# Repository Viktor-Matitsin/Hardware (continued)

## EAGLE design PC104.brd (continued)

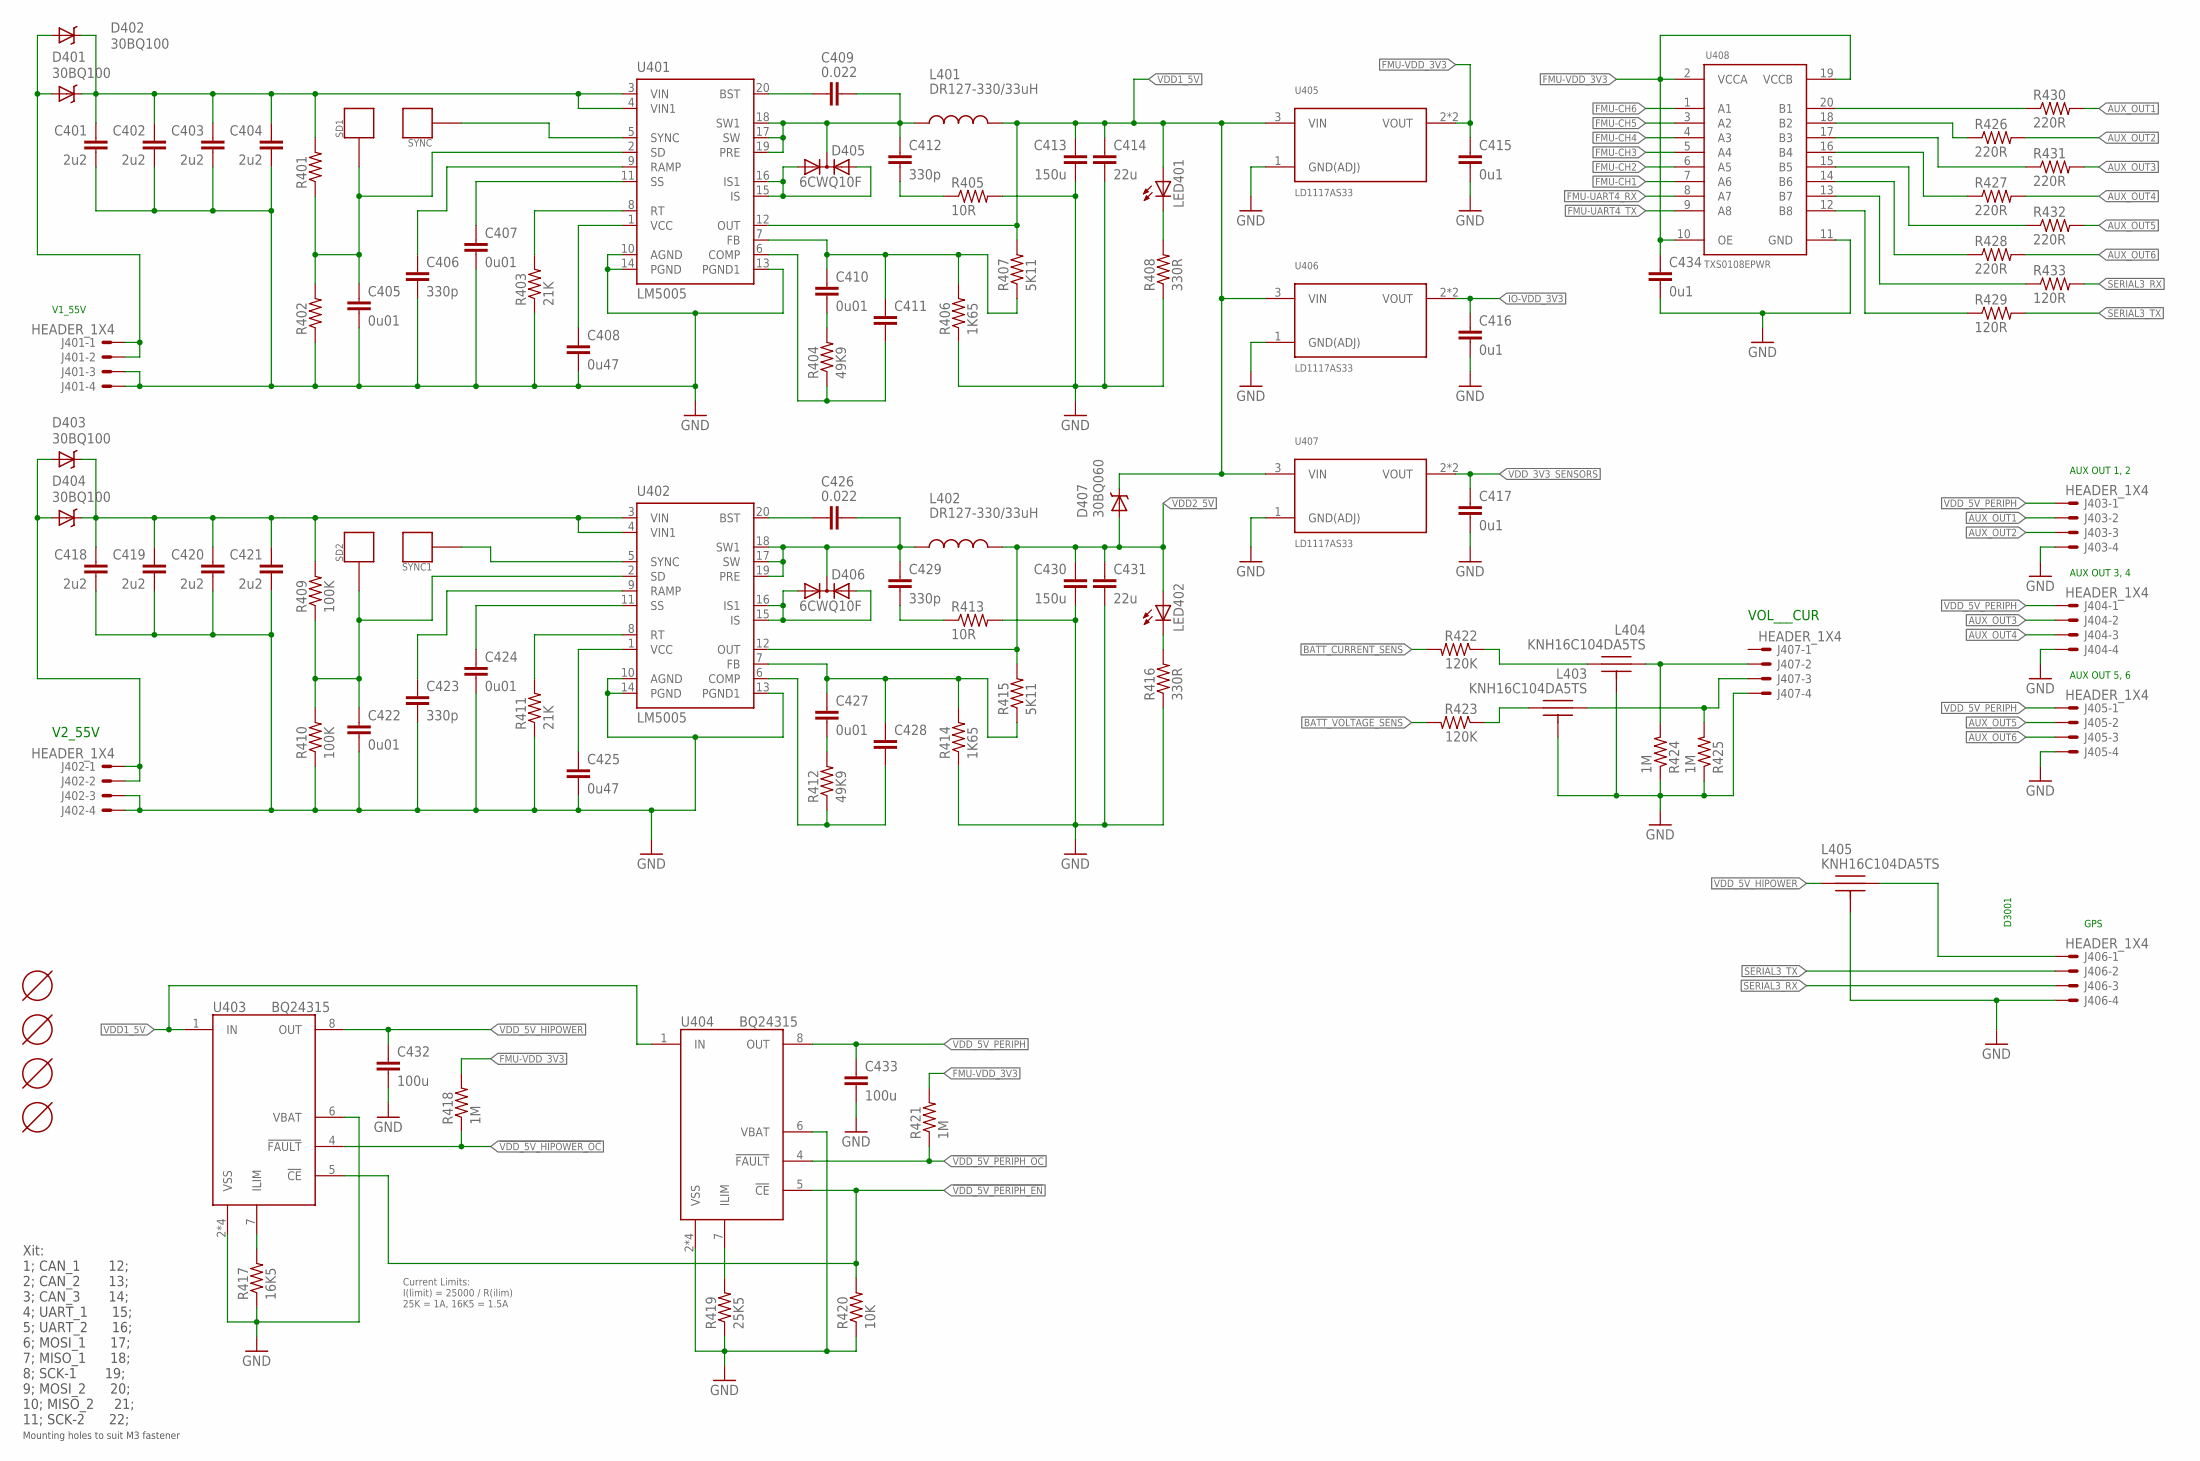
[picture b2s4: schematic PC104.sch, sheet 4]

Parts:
C401, C402, C403, C404, C418, C419, C420, C421: 2u2; 1812-CAP
C405, C407, C410, C422, C424, C427: 0u01; 0805-CAP
C406, C412, C423, C429: 330p; 0805-CAP
C408, C425: 0u47; 0805-CAP
C409, C426: 0.022; 0805-CAP
C411, C428: CAP0805; 0805-CAP
C413, C430: 150u; 1206-CAP
C414, C431: 22u; 1206-CAP
C415, C416, C417: 0u1; 0805-CAP
C432, C433: 100u; 1206-CAP
C434: 0u1; 0603-CAP
D401, D402, D403, D404: 30BQ100; SMA-DIODE
D405, D406: 6CWQ10F; SOT23
D407: 30BQ060; SMA-DIODE
J401, J402, J403, J404, J405, J406, J407: HEADER_1X4; HEADER_2.54MM-1X04
L401, L402: DR127-330/33uH; SLF10145
L403, L404, L405: KNH16C104DA5TS; KYOCERA-KNH16-DA
LED401, LED402: LED0603; 0603-LED
R401, R402: RESISTOR0805; 0805
R403, R411: 21K; 0805
R404, R412: 49K9; 0805
R405, R413: 10R; R2512
R406, R414: 1K65; 0805
R407, R415: 5K11; 0805
R408, R416: 330R; 0805
R409, R410: 100K; 0805
R417: 16K5; 0603-RES
R418, R421, R424, R425: 1M; 0603-RES
R419: 25K5; 0603-RES
R420: 10K; 0603-RES
R422, R423: 120K; 0603-RES
R426, R427, R428, R430, R431, R432: 220R; 0603-RES
R429, R433: 120R; 0603-RES
SD1, SD2: CYNC; PAD.03X.03
SYNC, SYNC1: CYNC; PAD.03X.03
U401, U402: LM5005; TSSOP20
U403, U404: BQ24315; QFN8-DSG
U405, U406, U407: LD1117AS33; SOT-223
U408: TXS0108EPWR; R-PDSO-G20
U$1, U$2, U$3, U$4: MOUNT-HOLE; MOUNT-HOLE3.3

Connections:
!VDD_5V_HIPOWER_OC: R418.1, U403.4 (!FAULT); also elsewhere on the board
!VDD_5V_PERIPH_EN: R420.2, U403.5 (!CE), U404.5 (!CE); also elsewhere on the board
!VDD_5V_PERIPH_OC: R421.1, U404.4 (!FAULT); also elsewhere on the board
+55V1: D401.A, D402.A, J401.1, J401.2
+55V1_V: C401.1, C402.1, C403.1, C404.1, D401.C, D402.C, R401.2, U401.3 (VIN), U401.4 (VIN1)
+55V2: D403.A, D404.A, J402.1, J402.2
+55V2_V: C418.1, C419.1, C420.1, C421.1, D403.C, D404.C, R409.2, U402.3 (VIN), U402.4 (VIN1)
AUX_OUT1: J403.2, R430.2
AUX_OUT2: J403.3, R426.2
AUX_OUT3: J404.2, R431.2
AUX_OUT4: J404.3, R427.2
AUX_OUT5: J405.2, R432.2
AUX_OUT6: J405.3, R428.2
BATT_CURRENT_SENS: R422.2; also elsewhere on the board
BATT_VOLTAGE_SENS: R423.2; also elsewhere on the board
D1X: C409.P$1 (1), C412.P$1 (1), D405.3 (C), L401.P$1 (1), U401.17 (SW), U401.18 (SW1), U401.19 (PRE)
D1_O: D405.1 (A1), D405.2 (A2), U401.15 (IS), U401.16 (IS1)
D2X: C426.P$1 (1), C429.P$1 (1), D406.3 (C), L402.P$1 (1), U402.17 (SW), U402.18 (SW1), U402.19 (PRE)
D2_O: D406.1 (A1), D406.2 (A2), U402.15 (IS), U402.16 (IS1)
FMU-CH1: U408.7 (A6); also elsewhere on the board
FMU-CH2: U408.6 (A5); also elsewhere on the board
FMU-CH3: U408.5 (A4); also elsewhere on the board
FMU-CH4: U408.4 (A3); also elsewhere on the board
FMU-CH5: U408.3 (A2); also elsewhere on the board
FMU-CH6: U408.1 (A1); also elsewhere on the board
FMU-UART4_RX: U408.8 (A7); also elsewhere on the board
FMU-UART4_TX: U408.9 (A8); also elsewhere on the board
FMU-VDD_3V3: C415.P$1 (1), C434.P$1 (1), R418.2, R421.2, U405.2 (VOUT), U405.4 (VOUT), U408.2 (VCCA), U408.10 (OE), U408.19 (VCCB); also elsewhere on the board
GND: C401.2, C402.2, C403.2, C404.2, C405.P$2 (2), C406.P$2 (2), C407.P$2 (2), C408.P$2 (2), C413.P$2 (2), C414.P$2 (2), C415.P$2 (2), C416.P$2 (2), C417.P$2 (2), C418.2, C419.2, C420.2, C421.2, C422.P$2 (2), C423.P$2 (2), C424.P$2 (2), C425.P$2 (2), C430.P$2 (2), C431.P$2 (2), C432.P$2 (2), C433.P$2 (2), C434.P$2 (2), J401.3, J401.4, J402.3, J402.4, J403.4, J404.4, J405.4, J406.4, J407.4, L403.P$3, L403.P$4, L403.P$5, L404.P$3, L404.P$4, L404.P$5, L405.P$3, L405.P$4, L405.P$5, R402.1, R403.1, R405.2, R406.1, R408.1, R410.1, R411.1, R413.2, R414.1, R416.1, R417.1, R419.1, R420.1, R424.1, R425.1, U401.10 (AGND), U401.13 (PGND1), U401.14 (PGND), U402.10 (AGND), U402.13 (PGND1), U402.14 (PGND), U403.2 (VSS), U403.6 (VBAT), U403.GND (VSS), U403.P$2 (VSS), U403.P$3 (VSS), U404.2 (VSS), U404.6 (VBAT), U404.GND (VSS), U404.P$2 (VSS), U404.P$3 (VSS), U405.1 (GND(ADJ)), U406.1 (GND(ADJ)), U407.1 (GND(ADJ)), U408.11 (GND); also elsewhere on the board
GPS: J406.1, L405.P$2
IO-VDD_3V3: C416.P$1 (1), U406.2 (VOUT), U406.4 (VOUT); also elsewhere on the board
unnamed: SYNC.P$1, U401.5 (SYNC)
unnamed: SYNC1.P$1, U402.5 (SYNC)
unnamed: L404.P$2, R422.1
unnamed: L403.P$2, R423.1
unnamed: J407.2, L404.P$1, R424.2
unnamed: J407.3, L403.P$1, R425.2
unnamed: R433.1, U408.13 (B7)
unnamed: C405.P$1 (1), R401.1, R402.2, SD1.P$1, U401.2 (SD)
unnamed: C412.P$2 (2), R405.1
unnamed: R429.1, U408.12 (B8)
unnamed: LED402.C, R416.2
unnamed: C407.P$1 (1), U401.11 (SS)
unnamed: C411.P$2 (2), R404.1, U401.6 (COMP)
unnamed: R403.2, U401.8 (RT)
unnamed: C409.P$2 (2), U401.20 (BST)
unnamed: C408.P$1 (1), U401.1 (VCC)
unnamed: LED401.C, R408.2
unnamed: R417.2, U403.7 (ILIM)
unnamed: C423.P$1 (1), U402.9 (RAMP)
unnamed: C410.P$1 (1), C411.P$1 (1), R406.2, R407.1, U401.7 (FB)
unnamed: C410.P$2 (2), R404.2
unnamed: C422.P$1 (1), R409.1, R410.2, SD2.P$1, U402.2 (SD)
unnamed: C424.P$1 (1), U402.11 (SS)
unnamed: R411.2, U402.8 (RT)
unnamed: C425.P$1 (1), U402.1 (VCC)
unnamed: C406.P$1 (1), U401.9 (RAMP)
unnamed: R430.1, U408.20 (B1)
unnamed: R426.1, U408.18 (B2)
unnamed: R431.1, U408.17 (B3)
unnamed: R427.1, U408.16 (B4)
unnamed: R432.1, U408.15 (B5)
unnamed: R428.1, U408.14 (B6)
unnamed: C426.P$2 (2), U402.20 (BST)
unnamed: C428.P$2 (2), R412.1, U402.6 (COMP)
unnamed: C429.P$2 (2), R413.1
unnamed: R419.2, U404.7 (ILIM)
unnamed: C427.P$1 (1), C428.P$1 (1), R414.2, R415.1, U402.7 (FB)
unnamed: C427.P$2 (2), R412.2
SERIAL3_RX: J406.3, R433.2
SERIAL3_TX: J406.2, R429.2
VDD1_5V: C413.P$1 (1), C414.P$1 (1), D407.C, L401.P$2 (2), LED401.A, R407.2, U401.12 (OUT), U403.1 (IN), U404.1 (IN), U405.3 (VIN), U406.3 (VIN), U407.3 (VIN); also elsewhere on the board
VDD2_5V: C430.P$1 (1), C431.P$1 (1), D407.A, L402.P$2 (2), LED402.A, R415.2, U402.12 (OUT)
VDD_3V3_SENSORS: C417.P$1 (1), U407.2 (VOUT), U407.4 (VOUT); also elsewhere on the board
VDD_5V_HIPOWER: C432.P$1 (1), L405.P$1, U403.8 (OUT); also elsewhere on the board
VDD_5V_PERIPH: C433.P$1 (1), J403.1, J404.1, J405.1, U404.8 (OUT); also elsewhere on the board

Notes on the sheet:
Mounting holes to suit M3 fastener
Xit: 1; CAN_1 12; 2; CAN_2 13; 3; CAN_3 14; 4; UART_1 15; 5; UART_2 16; 6; MOSI_1 17; 7; MISO_1 18; 8; SCK-1 19; 9; MOSI_2 20; 10; MISO_2 21; 11; SCK-2 22;
AUX OUT 1, 2
AUX OUT 3, 4
AUX OUT 5, 6
V1_55V
Current Limits: I(limit) = 25000 / R(ilim) 25K = 1A, 16K5 = 1.5A
D3001
GPS
VOL___CUR
V2_55V

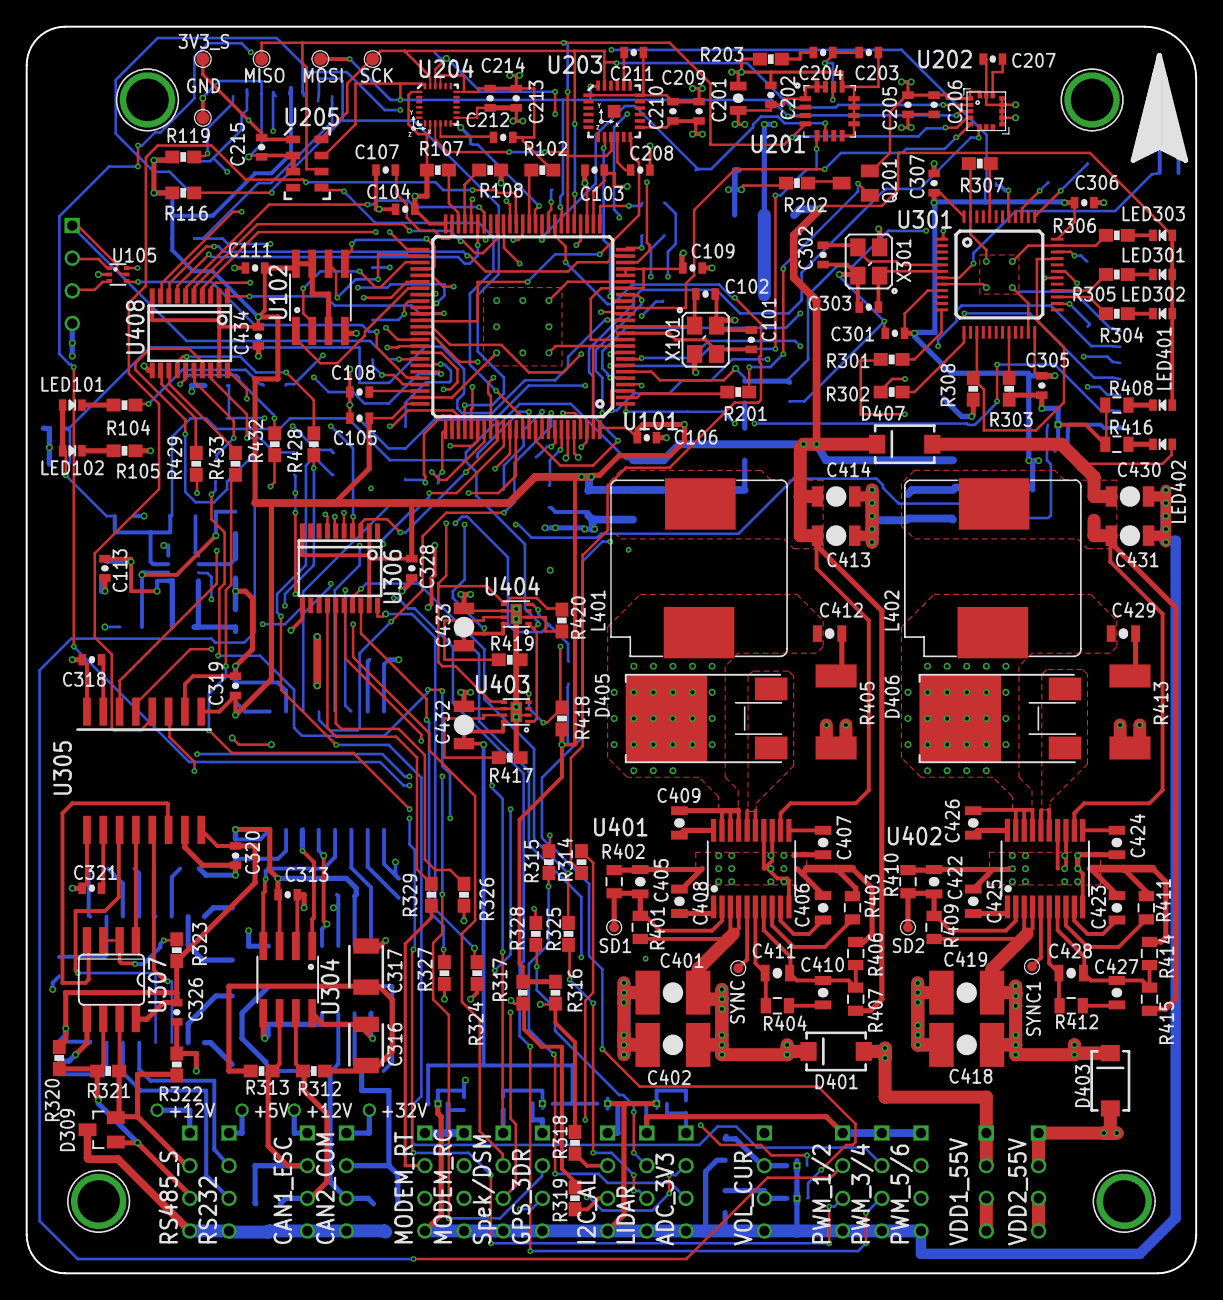
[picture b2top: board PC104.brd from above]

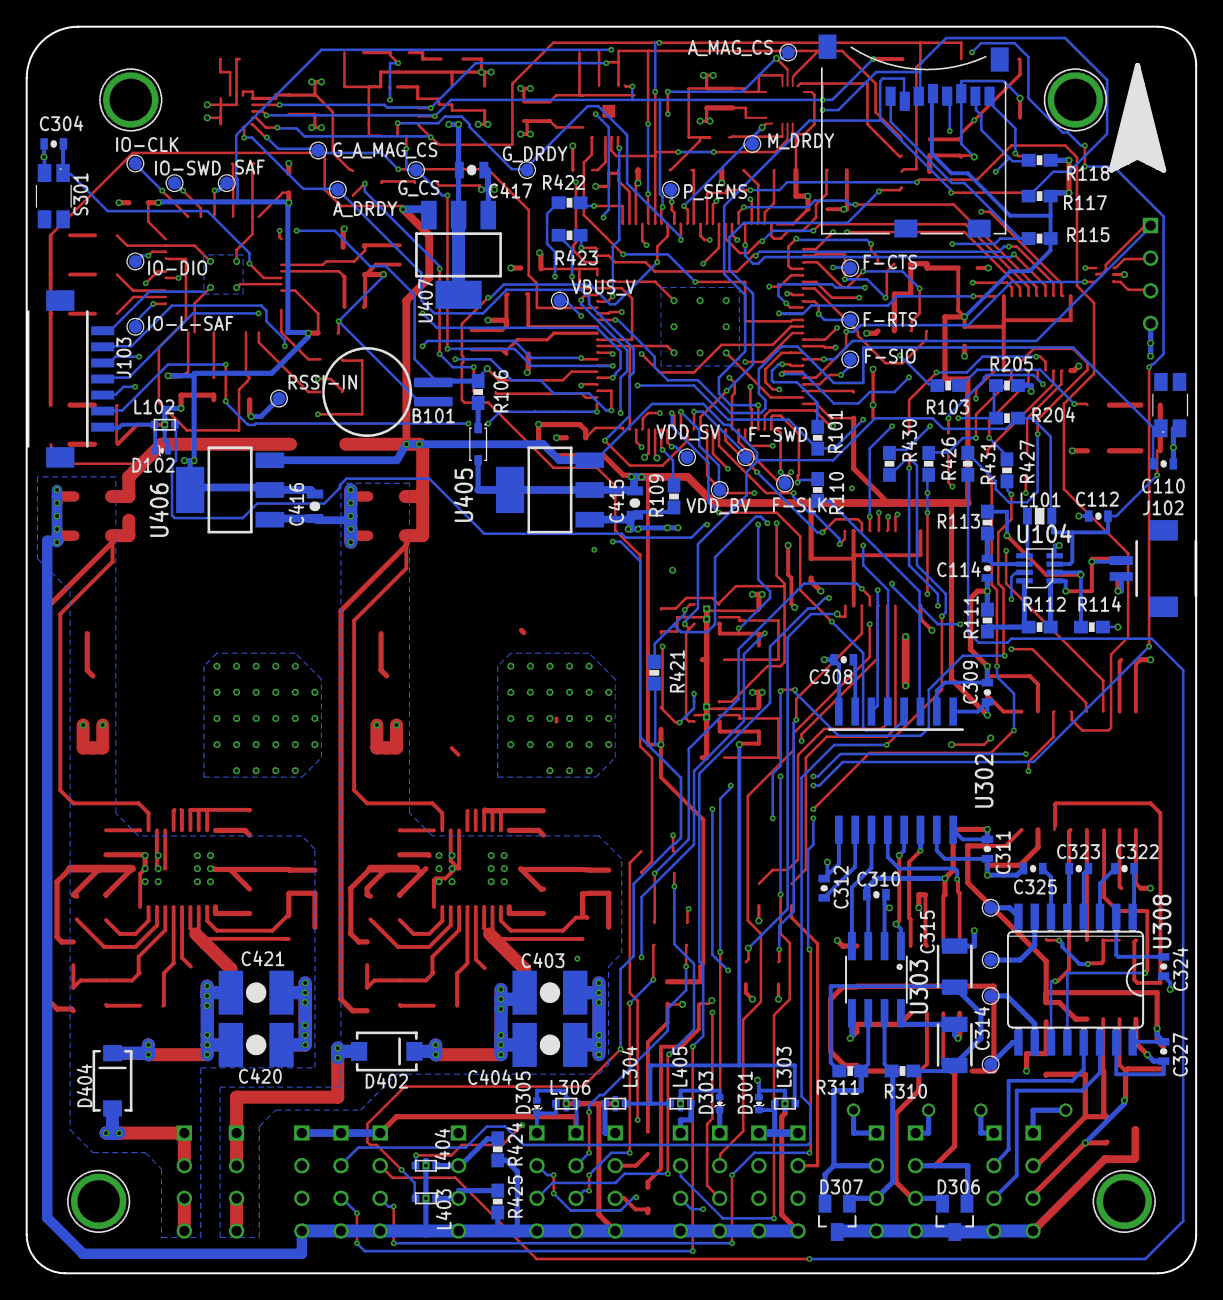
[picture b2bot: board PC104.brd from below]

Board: 4 copper layers, 91.0 x 97.0 mm, 298 parts (103 on the bottom side), 247 nets.

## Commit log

2017-08-15 Тестовый файлик
2017-08-15 Тест
2017-08-15 Текущая плата автопилота
2017-08-15 Изменили питание процессора
2017-08-15 Исправление #1
2017-08-22 Исправленно #7,#6. Кнопки BOOT 0 выведенны на пятаки #4.
2017-08-23 Исправленно #2, #3, #5, #8, #9
